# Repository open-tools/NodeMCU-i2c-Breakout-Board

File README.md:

# NodeMCU I²C and 1-Wire Breakout Board

Have you  ever tried connecting more than one I²C device to a NodeMCU board? While I²C and 1-wire are designed to allow dozens of devices connected to the same bus, most boards - including the NodeMCU - provide only one pin for the I²C lines (SCL and SDA). To connect multiple I²C devices, one usually needs to resolve to clumsy breadboards.

This board is a simple, small breakout board for the NodeMCU, which is attached to only one side of the NodeMCU. It provides multiple I²C and 1-wire connections. The pin order of the I²C connectors is the one used by most I²C sensors:
* VCC
* GND
* SCL
* SDA

Please note that the SparkFun sensors use a different order!

The pin order of the 1-Wire connectors is:
* GND
* DATA
* VCC

One can solder either male or female pin headers to the breakout board and connect the sensors using Dupont wires, or use female pin headers with the sensors directly plugged into the breakout board.

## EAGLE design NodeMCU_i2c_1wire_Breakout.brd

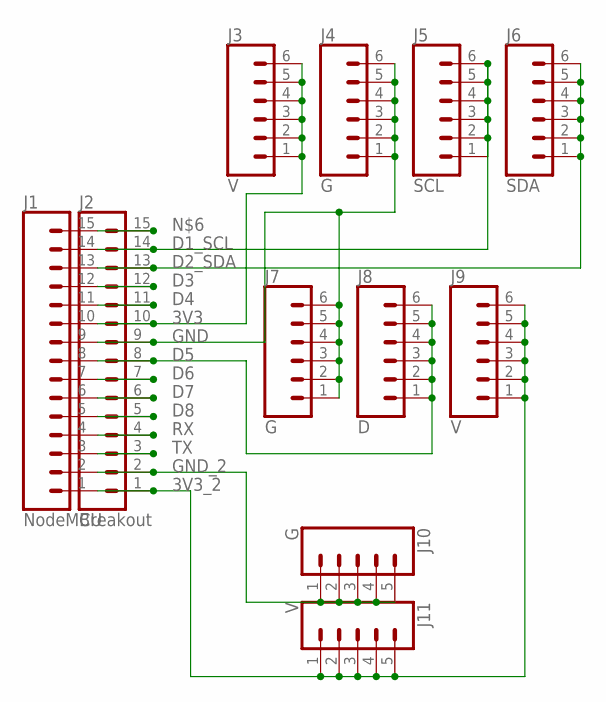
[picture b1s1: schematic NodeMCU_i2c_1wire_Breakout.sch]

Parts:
J1: NodeMCU; 1X15
J2: Breakout; 1X15
J3, J9: V; 1X06
J4, J7: G; 1X06
J5: SCL; 1X06
J6: SDA; 1X06
J8: D; 1X06
J10: G; 1X05
J11: V; 1X05

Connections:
3V3: J1.10, J2.10, J3.1, J3.2, J3.3, J3.4, J3.5, J3.6
3V3_2: J1.1, J2.1, J9.1, J9.2, J9.3, J9.4, J9.5, J9.6, J11.1, J11.2, J11.3, J11.4, J11.5
D1_SCL: J1.14, J2.14, J5.1, J5.2, J5.3, J5.4, J5.5, J5.6
D2_SDA: J1.13, J2.13, J6.1, J6.2, J6.3, J6.4, J6.5, J6.6
D3: J1.12, J2.12
D4: J1.11, J2.11
D5: J1.8, J2.8, J8.1, J8.2, J8.3, J8.4, J8.5, J8.6
D6: J1.7, J2.7
D7: J1.6, J2.6
D8: J1.5, J2.5
GND: J1.9, J2.9, J4.1, J4.2, J4.3, J4.4, J4.5, J4.6, J7.1, J7.2, J7.3, J7.4, J7.5, J7.6
GND_2: J1.2, J2.2, J10.1, J10.2, J10.3, J10.4, J10.5
unnamed: J1.15, J2.15
RX: J1.4, J2.4
TX: J1.3, J2.3

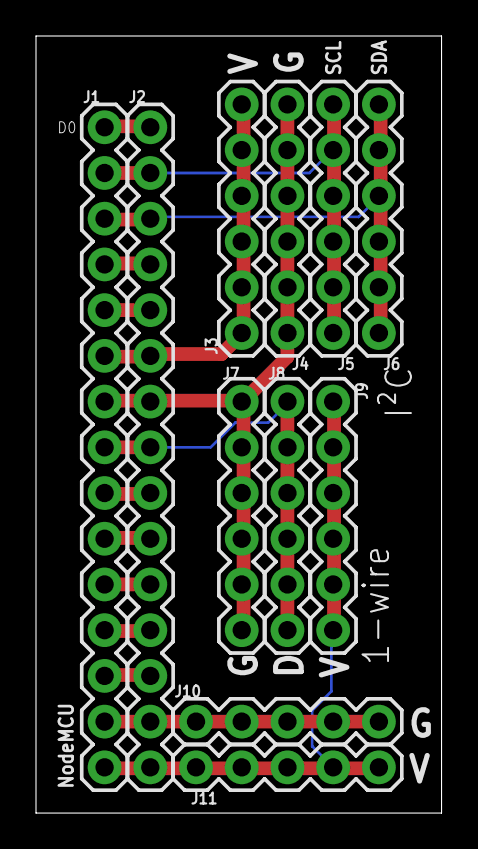
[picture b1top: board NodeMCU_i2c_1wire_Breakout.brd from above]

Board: 2 copper layers, 22.5 x 43.2 mm, 11 parts (0 on the bottom side), 15 nets.

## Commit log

2017-12-08 Add board and images
2017-12-08 Update README.md with description and images
2017-12-08 Use relative image paths in README.md

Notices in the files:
NodeMCU_i2c_1wire_Breakout.brd:
Licensed under CERN OHL v.1.2
parts and their libraries:
SparkFun-Connectors: Licensing: Creative Commons ShareAlike 4.0 International - https://creativecommons.org/licenses/by-sa/4.0
